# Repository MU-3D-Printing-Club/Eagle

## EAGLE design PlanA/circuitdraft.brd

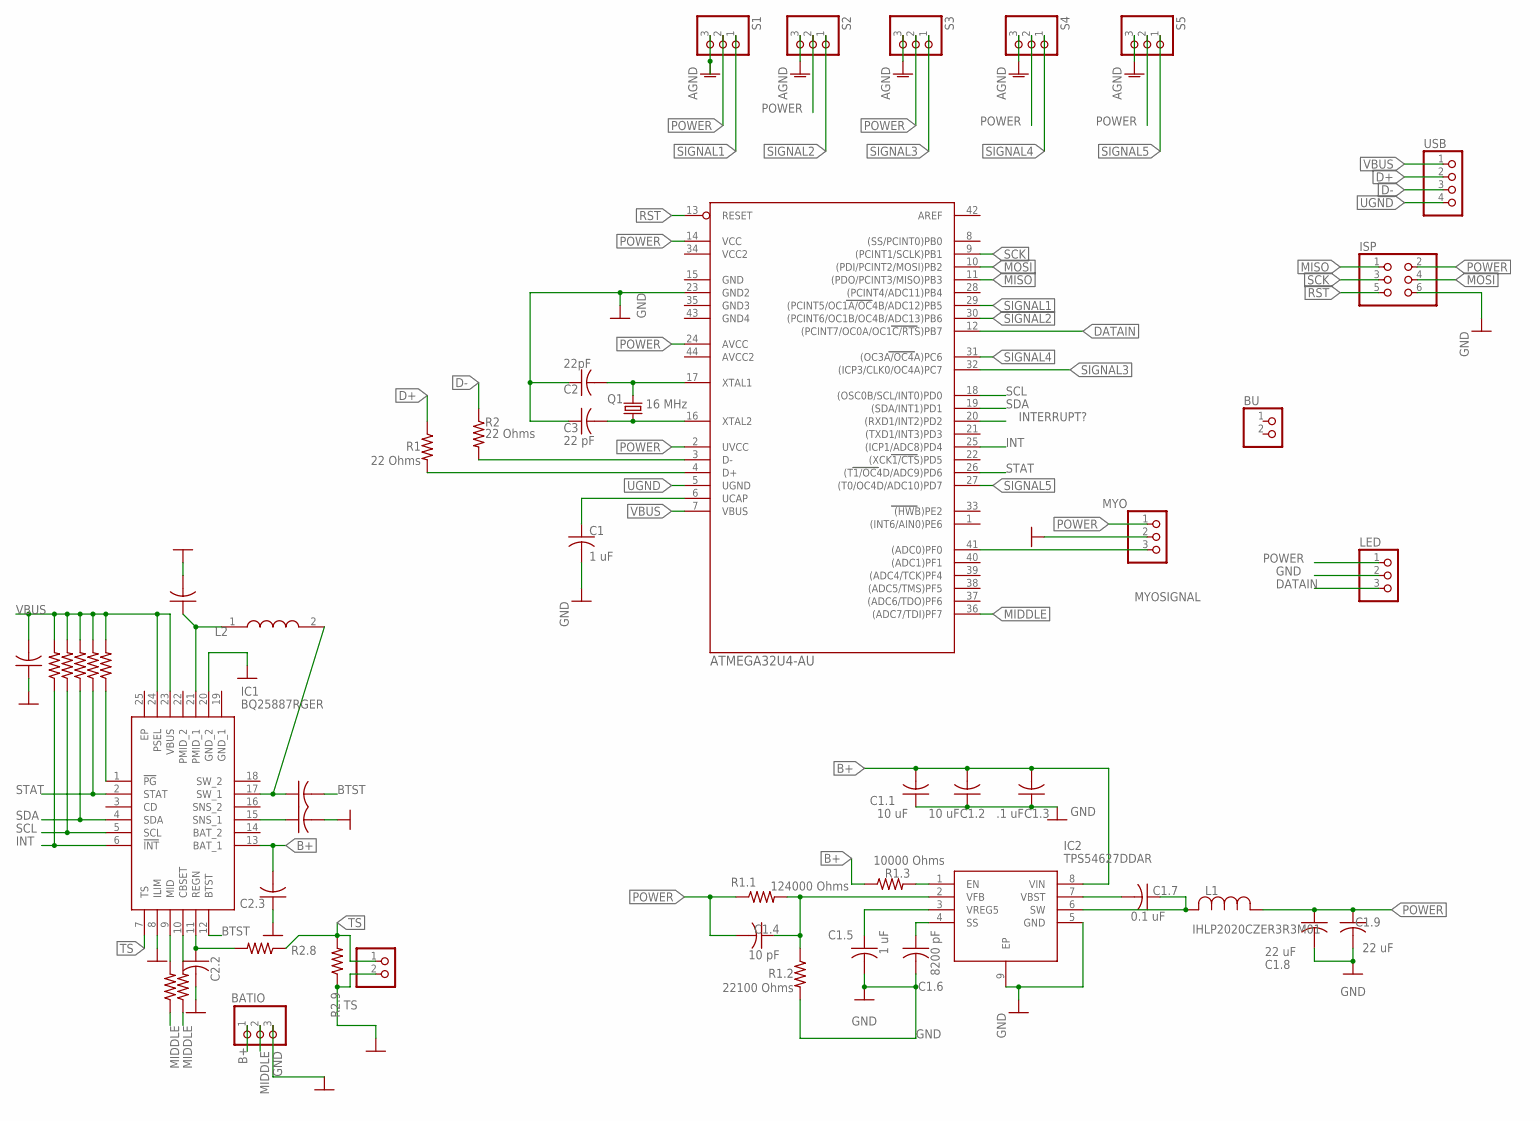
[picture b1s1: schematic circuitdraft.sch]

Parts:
BATIO: PINHD-1X3; 1X03
BU: PINHD-1X2; 1X02
C1, C1.5, C2.1, C2.3: 1 uF; C0603
C1.1, C1.2, C2.6: 10 uF; C0603
C1.3: .1 uF; C0603
C1.4: 10 pF; C0603
C1.6: 8200 pF; C0603
C1.7: 0.1 uF; C0603
C1.8, C1.9: 22 uF; C0603
C2: 22pF; C0603
C2.2: 4.7 uF; C0603
C2.4: 44 uF; C0603
C2.5: 47 nF; C0603
C3: 22 pF; C0603
IC1: BQ25887RGER; QFN50P400X400X100-25N
IC2: TPS54627DDAR; SOIC127P600X170-9N
ISP: PINHD-2X3; 2X03
L1: IHLP2020CZER3R3M01; IND_IHLP-2020CZ
L2: 1 uH; INDC2016X100N
LED: PINHD-1X3; 1X03
MYO: PINHD-1X3; 1X03
Q1: 16 MHz; 2.0X1.6_KX-5
R1, R2: 22 Ohms; R0603
R1.1: 124000 Ohms; R0603
R1.2: 22100 Ohms; R0603
R1.3, R2.1, R2.2, R2.3, R2.4, R2.5: 10000 Ohms; R0603
R2.6: 300 Ohms; R0603
R2.7: 12 Ohms; R0603
R2.8: 5.23 kOhms; R0603
R2.9: 30.1 kOhms; R0603
S1, S2, S3, S4, S5: PINHD-1X3; 1X03
TS: PINHD-1X2; 1X02
U$1: ATMEGA32U4-AU; TQFP44
USB: PINHD-1X4; 1X04

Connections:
B+: BATIO.1, C1.1.2, C1.2.2, C1.3.2, C2.3.2, IC1.13 (BAT_1), IC2.8 (VIN), R1.3.1
BTST: C2.5.2, IC1.12 (BTST)
D+: R1.1, USB.2
D-: R2.1, USB.3
DATAIN: LED.3, U$1.12 ((PCINT7/OC0A/OC1C/RTS)PB7)
GND: BATIO.3, C1.2, C1.1.1, C1.2.1, C1.3.1, C1.5.2, C1.6.2, C1.8.2, C1.9.2, C2.1, C2.1.1, C2.2.2, C2.3.1, C2.4.2, C2.6.2, C3.1, IC1.8 (ILIM), IC1.20 (GND_2), IC2.5 (GND), IC2.9 (EP), ISP.6, LED.2, MYO.2, R1.2.2, R2.9.1, S1.3, S2.3, S3.3, S4.3, S5.3, TS.2, U$1.23 (GND2)
INT: IC1.6 (!INT), R2.1.1, U$1.25 ((ICP1/ADC8)PD4)
INTERRUPT?: U$1.20 ((RXD1/INT2)PD2)
MIDDLE: BATIO.2, R2.6.1, R2.7.1, U$1.36 ((ADC7/TDI)PF7)
MISO: ISP.1, U$1.11 ((PDO/PCINT3/MISO)PB3)
MOSI: ISP.4, U$1.10 ((PDI/PCINT2/MOSI)PB2)
MYOSIGNAL: MYO.3, U$1.41 ((ADC0)PF0)
unnamed: IC2.1 (EN), R1.3.2
unnamed: R2.2, U$1.3 (D-)
unnamed: IC1.10 (CBSET), R2.7.2
unnamed: R1.2, U$1.4 (D+)
unnamed: C3.2, Q1.1, U$1.16 (XTAL2)
unnamed: C2.2, Q1.3 (2), U$1.17 (XTAL1)
unnamed: IC1.1 (!PG), R2.5.1
unnamed: C1.1, U$1.6 (UCAP)
unnamed: C1.6.1, IC2.4 (SS)
unnamed: IC1.9 (MID), R2.6.2
unnamed: C1.4.1, IC2.2 (VFB), R1.1.2, R1.2.1
unnamed: C1.5.1, IC2.3 (VREG5)
unnamed: C1.7.1, IC2.6 (SW), L1.2
unnamed: C1.7.2, IC2.7 (VBST)
unnamed: C2.5.1, IC1.17 (SW_1), L2.2
unnamed: C2.2.1, IC1.11 (REGN), R2.8.2
unnamed: C2.4.1, IC1.15 (SNS_1)
unnamed: C2.6.1, IC1.21 (PMID_1), L2.1
POWER: C1.4.2, C1.8.1, C1.9.1, ISP.2, L1.1, LED.1, MYO.1, R1.1.1, S1.2, S2.2, S3.2, S4.2, S5.2, U$1.2 (UVCC), U$1.14 (VCC), U$1.24 (AVCC)
RST: ISP.5, U$1.13 (RESET)
SCK: ISP.3, U$1.9 ((PCINT1/SCLK)PB1)
SCL: IC1.5 (SCL), R2.2.1, U$1.18 ((OSC0B/SCL/INT0)PD0)
SDA: IC1.4 (SDA), R2.3.1, U$1.19 ((SDA/INT1)PD1)
SIGNAL1: S1.1, U$1.29 ((PCINT5/OC1A/OC4B/ADC12)PB5)
SIGNAL2: S2.1, U$1.30 ((PCINT6/OC1B/OC4B/ADC13)PB6)
SIGNAL3: S3.1, U$1.32 ((ICP3/CLK0/OC4A)PC7)
SIGNAL4: S4.1, U$1.31 ((OC3A/OC4A)PC6)
SIGNAL5: S5.1, U$1.27 ((T0/OC4D/ADC10)PD7)
STAT: IC1.2 (STAT), R2.4.1, U$1.26 ((T1/OC4D/ADC9)PD6)
TS: IC1.7 (TS), R2.8.1, R2.9.2, TS.1
UGND: U$1.5 (UGND), USB.4
VBUS: C2.1.2, IC1.23 (VBUS), IC1.24 (PSEL), R2.1.2, R2.2.2, R2.3.2, R2.4.2, R2.5.2, U$1.7 (VBUS), USB.1

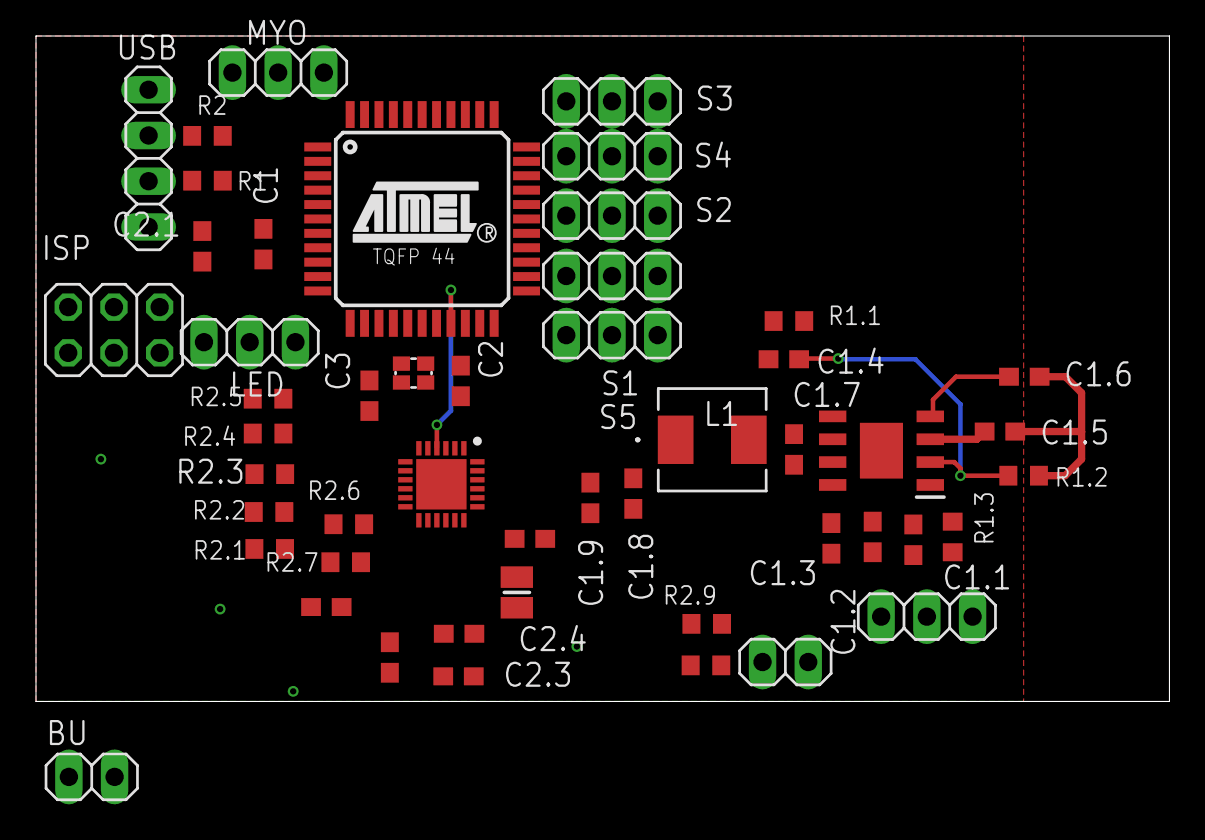
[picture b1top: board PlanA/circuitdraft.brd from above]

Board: 2 copper layers, 63.0 x 37.0 mm, 50 parts (0 on the bottom side), 43 nets.

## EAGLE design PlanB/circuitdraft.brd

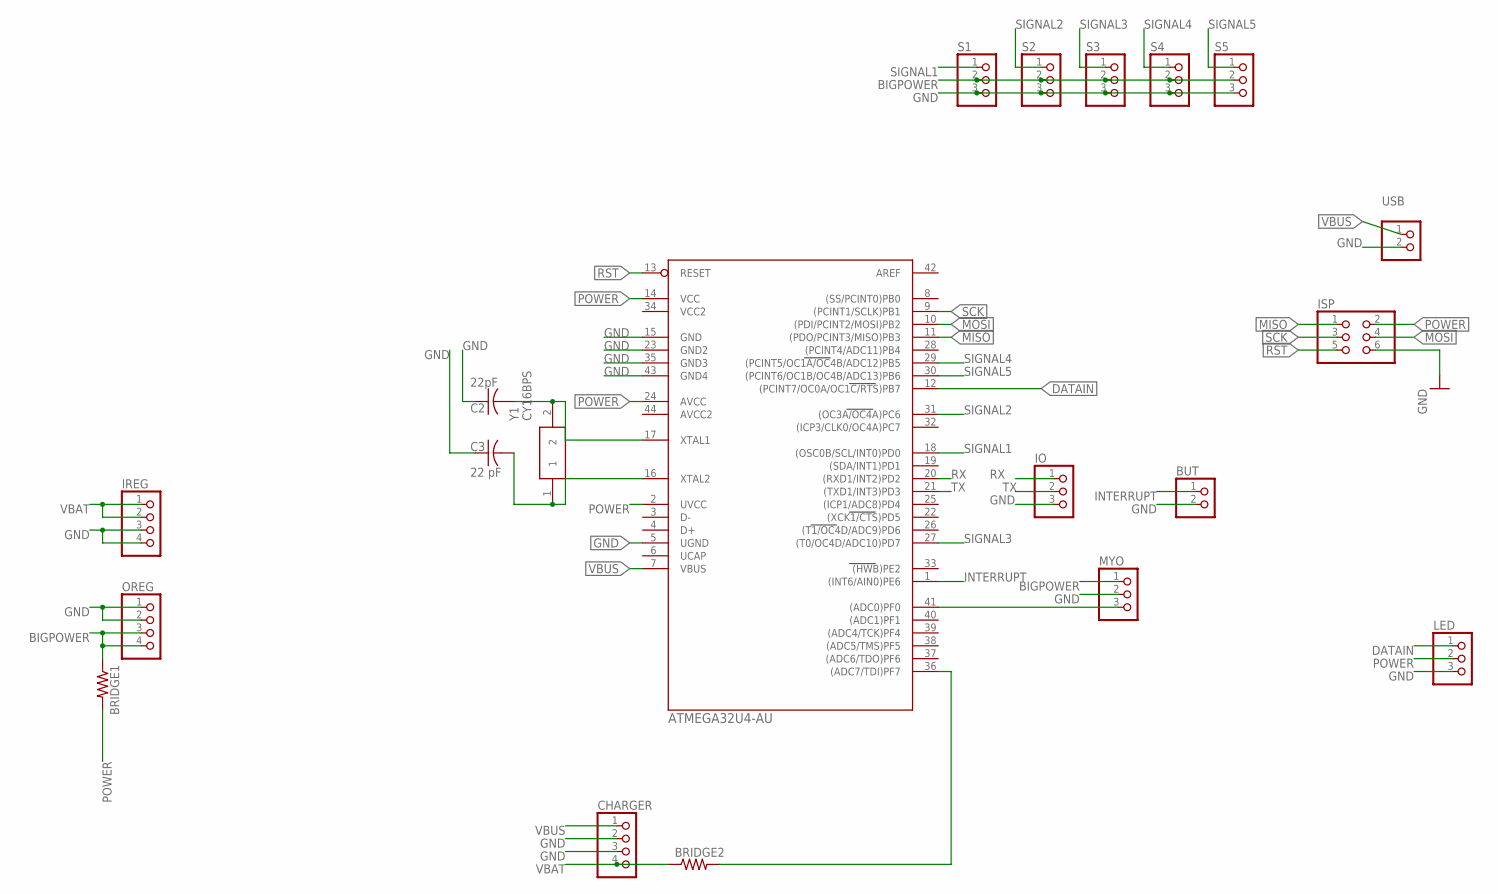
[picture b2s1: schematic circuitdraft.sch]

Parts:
BRIDGE1, BRIDGE2: R-US_M0805; M0805
BUT: PINHD-1X2; 1X02
C2: 22pF; C025-024X044
C3: 22 pF; C025-024X044
CHARGER: PINHD-1X4; 1X04
IO: PINHD-1X3; 1X03
IREG: PINHD-1X4; 1X04
ISP: PINHD-2X3; 2X03
LED: PINHD-1X3; 1X03
MYO: PINHD-1X3; 1X03
OREG: PINHD-1X4; 1X04
S1, S2, S3, S4, S5: PINHD-1X3; 1X03
U$1: ATMEGA32U4-AU; TQFP44
USB: PINHD-1X2; 1X02
Y1: CY16BPS

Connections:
BIGPOWER: BRIDGE1.1, MYO.1, OREG.3, OREG.4, S1.2, S2.2, S3.2, S4.2, S5.2
DATAIN: LED.1, U$1.12 ((PCINT7/OC0A/OC1C/RTS)PB7)
GND: BUT.2, C2.1, C3.1, CHARGER.2, CHARGER.3, IO.3, IREG.3, IREG.4, ISP.6, LED.3, MYO.2, OREG.1, OREG.2, S1.3, S2.3, S3.3, S4.3, S5.3, U$1.5 (UGND), U$1.15 (GND), U$1.23 (GND2), U$1.35 (GND3), U$1.43 (GND4), USB.2
INTERRUPT: BUT.1, U$1.1 ((INT6/AIN0)PE6)
MISO: ISP.1, U$1.11 ((PDO/PCINT3/MISO)PB3)
MOSI: ISP.4, U$1.10 ((PDI/PCINT2/MOSI)PB2)
unnamed: MYO.3, U$1.41 ((ADC0)PF0)
unnamed: C2.2, U$1.17 (XTAL1), Y1.2
unnamed: C3.2, U$1.16 (XTAL2), Y1.1
unnamed: BRIDGE2.2, U$1.36 ((ADC7/TDI)PF7)
POWER: BRIDGE1.2, ISP.2, LED.2, U$1.2 (UVCC), U$1.14 (VCC), U$1.24 (AVCC)
RST: ISP.5, U$1.13 (RESET)
RX: IO.1, U$1.20 ((RXD1/INT2)PD2)
SCK: ISP.3, U$1.9 ((PCINT1/SCLK)PB1)
SIGNAL1: S1.1, U$1.18 ((OSC0B/SCL/INT0)PD0)
SIGNAL2: S2.1, U$1.31 ((OC3A/OC4A)PC6)
SIGNAL3: S3.1, U$1.27 ((T0/OC4D/ADC10)PD7)
SIGNAL4: S4.1, U$1.29 ((PCINT5/OC1A/OC4B/ADC12)PB5)
SIGNAL5: S5.1, U$1.30 ((PCINT6/OC1B/OC4B/ADC13)PB6)
TX: IO.2, U$1.21 ((TXD1/INT3)PD3)
VBAT: BRIDGE2.1, CHARGER.4, IREG.1, IREG.2
VBUS: CHARGER.1, U$1.7 (VBUS), USB.1

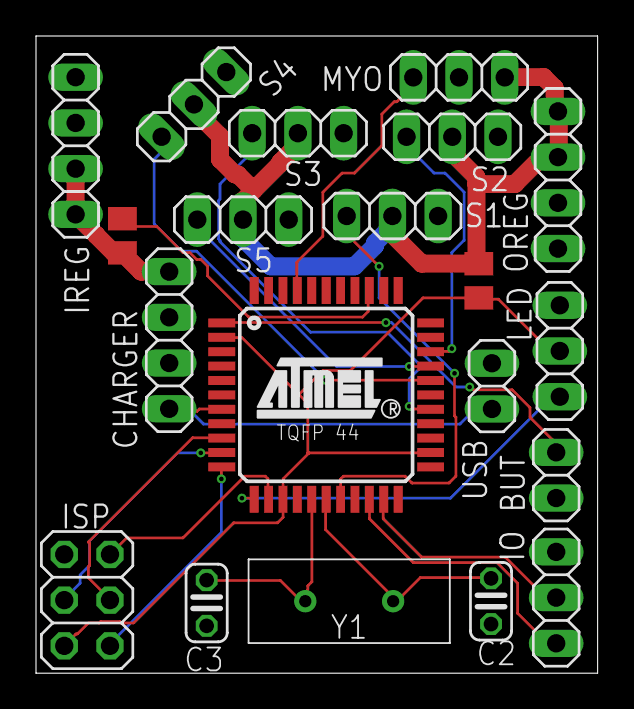
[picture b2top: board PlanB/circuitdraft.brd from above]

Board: 2 copper layers, 31.2 x 35.4 mm, 20 parts (0 on the bottom side), 22 nets.

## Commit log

2019-11-20 added biggnd and bigpower for large traces
2019-11-21 more ajustments
2019-11-21 refined board and fixed locations and orintations
2019-11-21 final refinement
2019-11-21 changed some pins to match arduino pins
2020-01-09 updated
    rotated servo ports
    removed unnecessary USB things
    moved some things around
2020-01-09 Error checking
2020-01-09 deleted old things
2020-01-09 Passes Oshpark DRU
2020-01-16 started on v2 board in kicad
2020-01-16 changed 3.3 regulator and added resistor to neopixel data input
2020-01-17 charger and 5v regulator added. should be ready for breadboard prototyping.
2020-01-18 starting pcb layout done
2020-01-19 moved parts to put logic on bottom of board
2020-01-19 finsihed first test routing(need thicker traces for power)
2020-01-20 added bigger traces to servo power but should be double checked
2020-01-21 added tx/rx and moved a few things
2020-01-21 shifted parts to give isp more room
2020-01-22 flipped ireg
2020-01-22 passed drc
2020-01-25 file rename

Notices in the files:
parts and their libraries:
crystal-geyer_V1_0: Copyright: Geyer-Electronic
